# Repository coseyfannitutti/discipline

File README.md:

# DISCIPLINE V2

**65% keyboard assembled with only through hole components, including usb type-c**

**[LICENSE](LICENSE)**

Discipline V2 is licensed under the [Creative Commons Attribution-NonCommercial 4.0 International License](https://creativecommons.org/licenses/by-nc/4.0/). 

This PCB design may be freely reproduced, modified, and manufactured for **PERSONAL USE ONLY** and may not be reproduced in physical form for public sale outside of [CFTKB.com](https://www.cftkb.com). 

If you have built upon this work and have changed the design in a significant way, the non-commercial clause can be waived. If you have developed your own design using files in this repository and would like to sell it, please contact me at bryan@cftkb.com. I fully support those looking to make new things and be creative and will more than likely approve and support your project.

**[BOM, Build Guide, and Flashing Information](./doc)**

**Kits available at [cftkb.com](https://www.cftkb.com)**

**[Optional High Profile Lasercut Acrylic Case](./acrylic-case)**

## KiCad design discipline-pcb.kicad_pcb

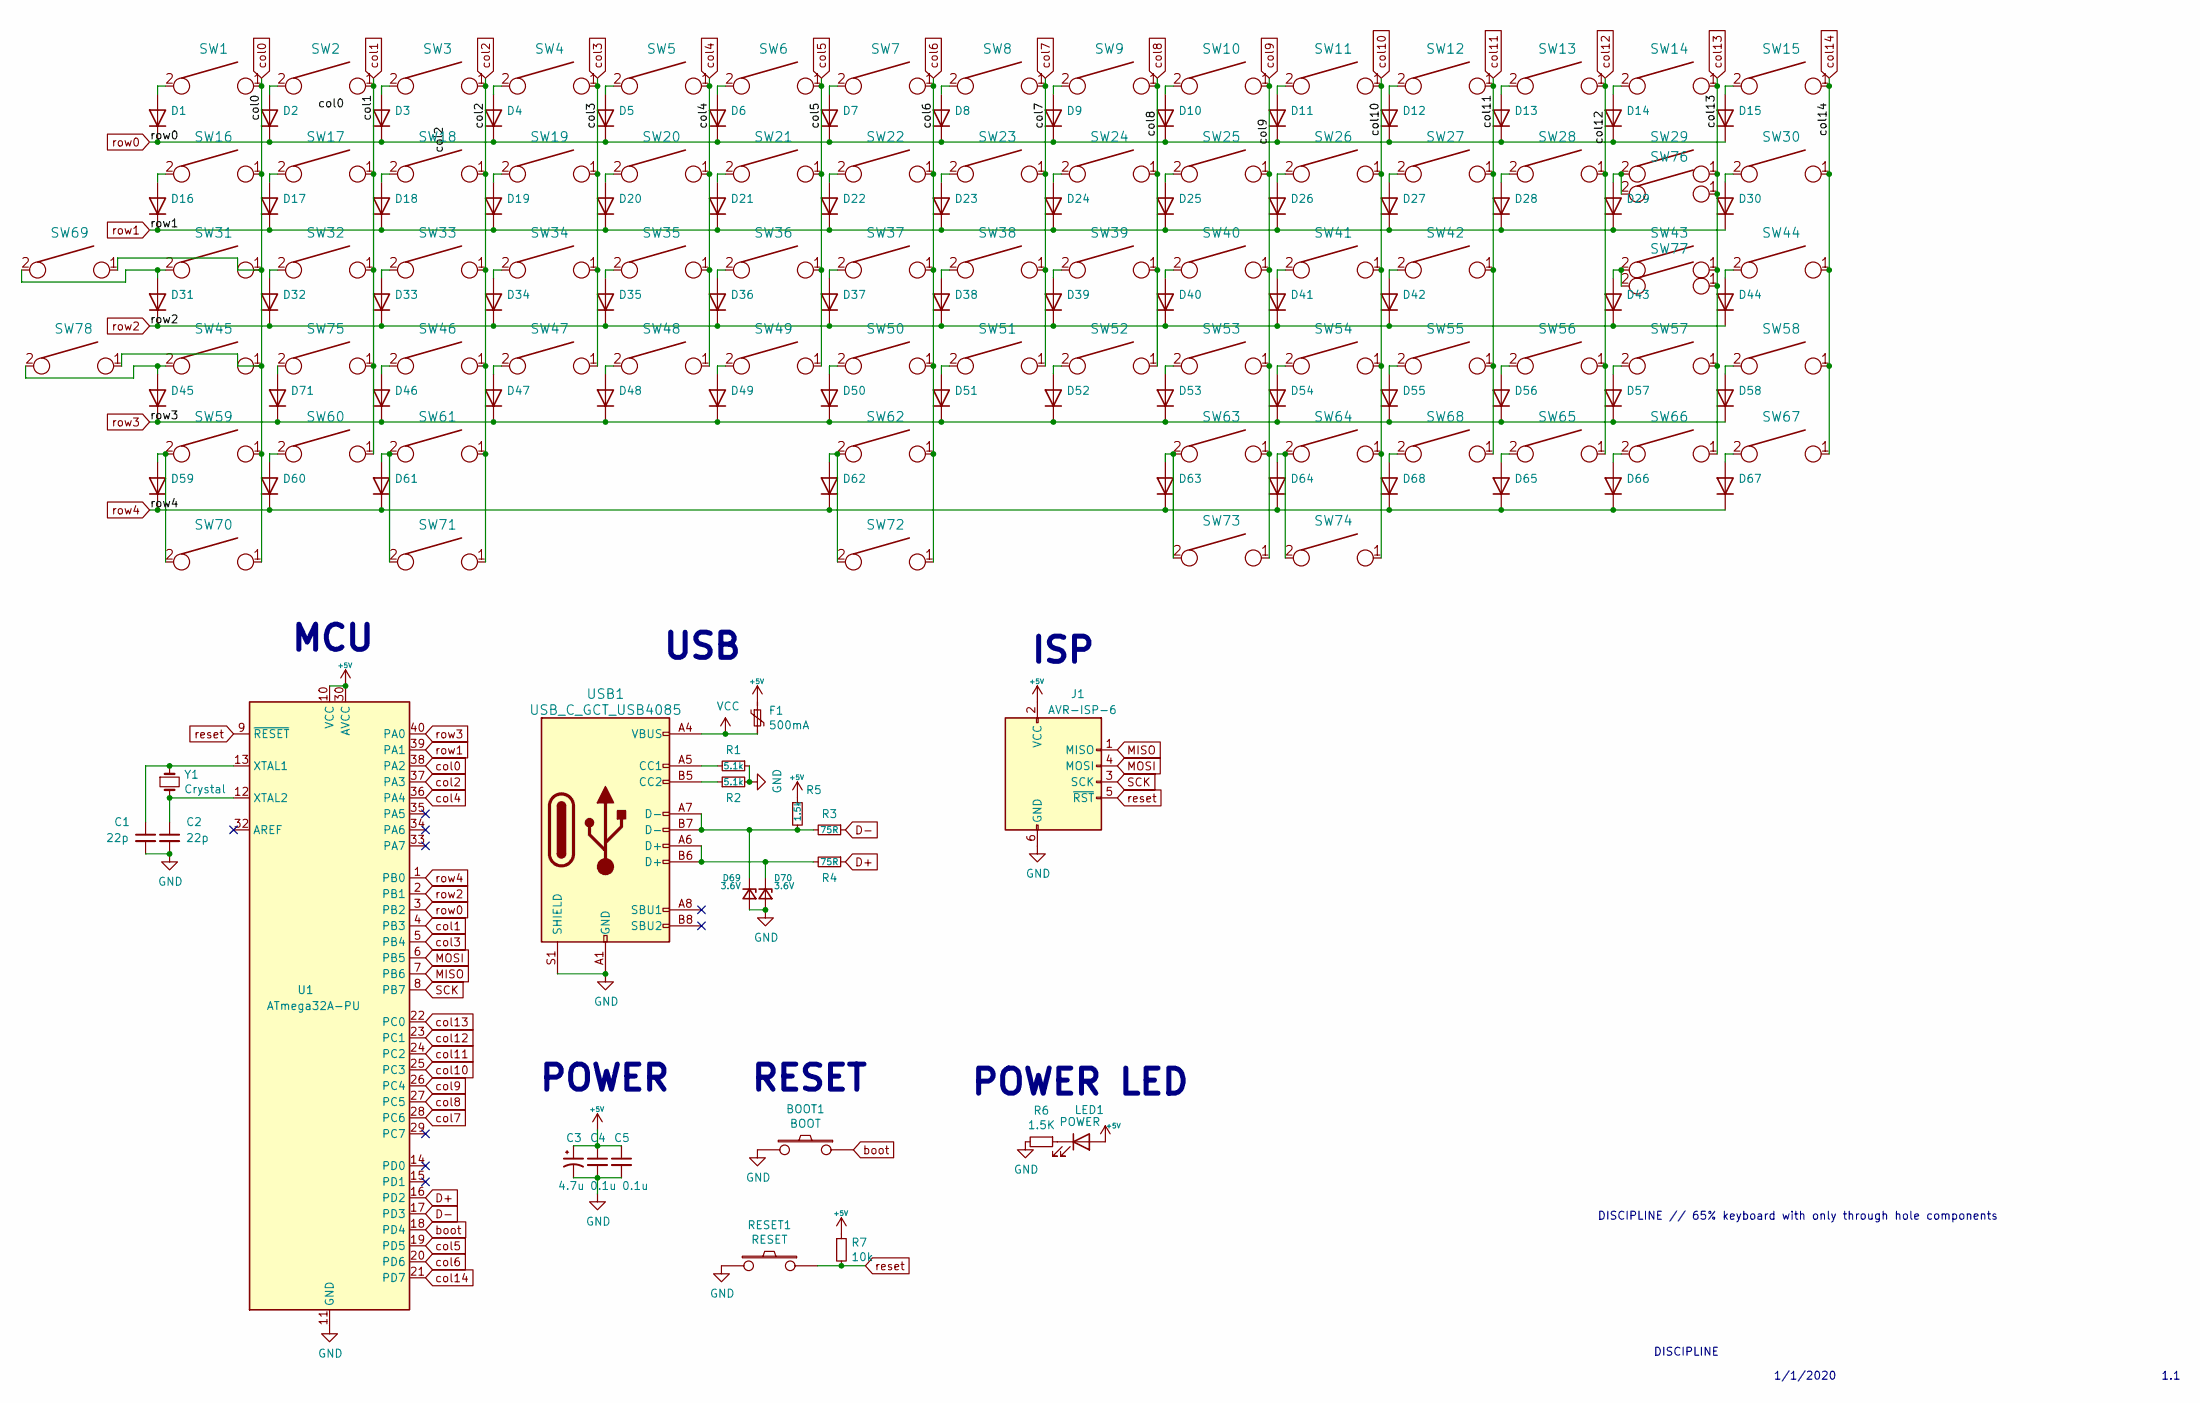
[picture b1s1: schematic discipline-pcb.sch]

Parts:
BOOT1: BOOT; SW_PUSH_6mm
C1, C2: 22p; C_Disc_D3.0mm_W1.6mm_P2.50mm
C3: 4.7u; CP_Radial_D4.0mm_P1.50mm
C4, C5: 0.1u; C_Disc_D4.3mm_W1.9mm_P5.00mm
D1, D2, D3, D4, D5, D6, D7, D8, D9, D10, D11, D12, D13, D14, D15, D16, D17, D18, D19, D20, D21, D22, D23, D24, D25, D26, D27, D28, D29, D30, D31, D32, D33, D34, D35, D36, D37, D38, D39, D40, D41, D42, D43, D44, D45, D46, D47, D48, D49, D50, D51, D52, D53, D54, D55, D56, D57, D58, D59, D60, D61, D62, D63, D64, D65, D66, D67, D68, D71: D_DO-35_SOD27_P5.08mm_Horizontal
D69, D70: 3.6V; D_DO-35_SOD27_P5.08mm_Horizontal
F1: 500mA; polyfuse_5.1mm
J1: AVR-ISP-6; AVR_ICSP_3x2
LED1: POWER; LED_D3.0mm
R1, R2: 5.1k; R_Axial_DIN0204_L3.6mm_D1.6mm_P5.08mm_Horizontal
R3, R4: 75R; R_Axial_DIN0204_L3.6mm_D1.6mm_P5.08mm_Horizontal
R5: 1.5k; R_Axial_DIN0204_L3.6mm_D1.6mm_P5.08mm_Horizontal
R6: 1.5K; R_Axial_DIN0204_L3.6mm_D1.6mm_P5.08mm_Horizontal
R7: 10k; R_Axial_DIN0204_L3.6mm_D1.6mm_P5.08mm_Horizontal
RESET1: RESET; SW_PUSH_6mm
SW1, SW2, SW3, SW4, SW5, SW6, SW7, SW8, SW9, SW10, SW11, SW12, SW13, SW15, SW17, SW18, SW19, SW20, SW21, SW22, SW23, SW24, SW25, SW26, SW27, SW28, SW30, SW32, SW33, SW34, SW35, SW36, SW37, SW38, SW39, SW40, SW41, SW42, SW44, SW46, SW47, SW48, SW49, SW50, SW51, SW52, SW53, SW54, SW55, SW57, SW58, SW62, SW65, SW66, SW67, SW68, SW72, SW75, SW77: KEYSW; SW_Cherry_MX1A_1.00u_PCB-NOSCREEN
SW14: KEYSW; SW_Cherry_MX1A_2.00u_PCBNOSCREEN
SW16, SW29, SW70, SW71, SW73, SW74: KEYSW; SW_Cherry_MX1A_1.50u_PCBNOSCREEN
SW31, SW56: KEYSW; SW_Cherry_MX1A_1.75u_PCBNOSCREEN
SW43, SW45: KEYSW; SW_Cherry_MX1A_2.25u_PCBNOSCREEN
SW59, SW60, SW61, SW63, SW64, SW69, SW78: KEYSW; SW_Cherry_MX1A_1.25u_PCBNOSCREEN
SW76: KEYSW; SW_Cherry_MX1A_ISOEnter_PCB_ReversedStabilizer
U1: ATmega32A-PU; DIP-40_W15.24mm
USB1: USB_C_GCT_USB4085
Y1: Crystal; Crystal_HC49-4H_Vertical

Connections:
+5V: C3.1, C4.1, C5.1, F1.1, J1.2 (VCC), LED1.2 (A), R5.1, R7.1, U1.10 (VCC), U1.30 (AVCC)
D+: R4.1, U1.16 (PD2)
D-: R3.1, U1.17 (PD3)
GND: BOOT1.2, C1.2, C2.2, C3.2, C4.2, C5.2, D69.2 (A), D70.2 (A), J1.6 (GND), R1.1, R2.2, R6.2, RESET1.2, U1.11 (GND), U1.31 (GND), USB1.A1 (GND), USB1.A12 (GND), USB1.B1 (GND), USB1.B12 (GND), USB1.S1 (SHIELD)
MISO: J1.1 (MISO), U1.7 (PB6)
MOSI: J1.4 (MOSI), U1.6 (PB5)
unnamed: C1.1, U1.13 (XTAL1), Y1.1
unnamed: C2.1, U1.12 (XTAL2), Y1.2
unnamed: D1.2 (A), SW1.2
unnamed: D2.2 (A), SW2.2
unnamed: D3.2 (A), SW3.2
unnamed: D4.2 (A), SW4.2
unnamed: D5.2 (A), SW5.2
unnamed: D6.2 (A), SW6.2
unnamed: D7.2 (A), SW7.2
unnamed: D8.2 (A), SW8.2
unnamed: D9.2 (A), SW9.2
unnamed: D10.2 (A), SW10.2
unnamed: D11.2 (A), SW11.2
unnamed: D12.2 (A), SW12.2
unnamed: D13.2 (A), SW13.2
unnamed: D14.2 (A), SW14.2
unnamed: D15.2 (A), SW15.2
unnamed: D16.2 (A), SW16.2
unnamed: D17.2 (A), SW17.2
unnamed: D18.2 (A), SW18.2
unnamed: D19.2 (A), SW19.2
unnamed: D20.2 (A), SW20.2
unnamed: D21.2 (A), SW21.2
unnamed: D22.2 (A), SW22.2
unnamed: D23.2 (A), SW23.2
unnamed: D24.2 (A), SW24.2
unnamed: D25.2 (A), SW25.2
unnamed: D26.2 (A), SW26.2
unnamed: D27.2 (A), SW27.2
unnamed: D28.2 (A), SW28.2
unnamed: D29.2 (A), SW29.2, SW76.2
unnamed: D30.2 (A), SW30.2
unnamed: D31.2 (A), SW31.2, SW69.2
unnamed: D32.2 (A), SW32.2
unnamed: D33.2 (A), SW33.2
unnamed: D34.2 (A), SW34.2
unnamed: D35.2 (A), SW35.2
unnamed: D36.2 (A), SW36.2
unnamed: D37.2 (A), SW37.2
unnamed: D38.2 (A), SW38.2
unnamed: D39.2 (A), SW39.2
unnamed: D40.2 (A), SW40.2
unnamed: D41.2 (A), SW41.2
unnamed: D42.2 (A), SW42.2
unnamed: D43.2 (A), SW43.2, SW77.2
unnamed: D44.2 (A), SW44.2
unnamed: D45.2 (A), SW45.2, SW78.2
unnamed: D46.2 (A), SW46.2
unnamed: D47.2 (A), SW47.2
unnamed: D48.2 (A), SW48.2
unnamed: D49.2 (A), SW49.2
unnamed: D50.2 (A), SW50.2
unnamed: D51.2 (A), SW51.2
unnamed: D52.2 (A), SW52.2
unnamed: D53.2 (A), SW53.2
unnamed: D54.2 (A), SW54.2
unnamed: D55.2 (A), SW55.2
unnamed: D56.2 (A), SW56.2
unnamed: D57.2 (A), SW57.2
unnamed: D58.2 (A), SW58.2
unnamed: D59.2 (A), SW59.2, SW70.2
unnamed: D60.2 (A), SW60.2
unnamed: D61.2 (A), SW61.2, SW71.2
unnamed: D62.2 (A), SW62.2, SW72.2
unnamed: D63.2 (A), SW63.2, SW73.2
unnamed: D64.2 (A), SW64.2, SW74.2
unnamed: D65.2 (A), SW65.2
unnamed: D66.2 (A), SW66.2
unnamed: D67.2 (A), SW67.2
unnamed: D68.2 (A), SW68.2
unnamed: D69.1 (K), R3.2, R5.2, USB1.A7 (D-), USB1.B7 (D-)
unnamed: D70.1 (K), R4.2, USB1.A6 (D+), USB1.B6 (D+)
unnamed: D71.2 (A), SW75.2
unnamed: LED1.1 (K), R6.1
unnamed: R1.2, USB1.A5 (CC1)
unnamed: R2.1, USB1.B5 (CC2)
SCK: J1.3 (SCK), U1.8 (PB7)
VCC: F1.2, USB1.A4 (VBUS), USB1.A9 (VBUS), USB1.B4 (VBUS), USB1.B9 (VBUS)
boot: BOOT1.1, U1.18 (PD4)
col0: SW1.1, SW16.1, SW31.1, SW45.1, SW59.1, SW69.1, SW70.1, SW78.1, U1.38 (PA2)
col1: SW2.1, SW17.1, SW32.1, SW60.1, SW75.1, U1.4 (PB3)
col2: SW3.1, SW18.1, SW33.1, SW46.1, SW61.1, SW71.1, U1.37 (PA3)
col3: SW4.1, SW19.1, SW34.1, SW47.1, U1.5 (PB4)
col4: SW5.1, SW20.1, SW35.1, SW48.1, U1.36 (PA4)
col5: SW6.1, SW21.1, SW36.1, SW49.1, U1.19 (PD5)
col6: SW7.1, SW22.1, SW37.1, SW50.1, SW62.1, SW72.1, U1.20 (PD6)
col7: SW8.1, SW23.1, SW38.1, SW51.1, U1.28 (PC6)
col8: SW9.1, SW24.1, SW39.1, SW52.1, U1.27 (PC5)
col9: SW10.1, SW25.1, SW40.1, SW53.1, SW63.1, SW73.1, U1.26 (PC4)
col10: SW11.1, SW26.1, SW41.1, SW54.1, SW64.1, SW74.1, U1.25 (PC3)
col11: SW12.1, SW27.1, SW42.1, SW55.1, SW68.1, U1.24 (PC2)
col12: SW13.1, SW28.1, SW56.1, SW65.1, U1.23 (PC1)
col13: SW14.1, SW29.1, SW43.1, SW57.1, SW66.1, SW76.1, SW77.1, U1.22 (PC0)
col14: SW15.1, SW30.1, SW44.1, SW58.1, SW67.1, U1.21 (PD7)
reset: J1.5 (~RST), R7.2, RESET1.1, U1.9 (~RESET)
row0: D1.1 (K), D2.1 (K), D3.1 (K), D4.1 (K), D5.1 (K), D6.1 (K), D7.1 (K), D8.1 (K), D9.1 (K), D10.1 (K), D11.1 (K), D12.1 (K), D13.1 (K), D14.1 (K), D15.1 (K), U1.3 (PB2)
row1: D16.1 (K), D17.1 (K), D18.1 (K), D19.1 (K), D20.1 (K), D21.1 (K), D22.1 (K), D23.1 (K), D24.1 (K), D25.1 (K), D26.1 (K), D27.1 (K), D28.1 (K), D29.1 (K), D30.1 (K), U1.39 (PA1)
row2: D31.1 (K), D32.1 (K), D33.1 (K), D34.1 (K), D35.1 (K), D36.1 (K), D37.1 (K), D38.1 (K), D39.1 (K), D40.1 (K), D41.1 (K), D42.1 (K), D43.1 (K), D44.1 (K), U1.2 (PB1)
row3: D45.1 (K), D46.1 (K), D47.1 (K), D48.1 (K), D49.1 (K), D50.1 (K), D51.1 (K), D52.1 (K), D53.1 (K), D54.1 (K), D55.1 (K), D56.1 (K), D57.1 (K), D58.1 (K), D71.1 (K), U1.40 (PA0)
row4: D59.1 (K), D60.1 (K), D61.1 (K), D62.1 (K), D63.1 (K), D64.1 (K), D65.1 (K), D66.1 (K), D67.1 (K), D68.1 (K), U1.1 (PB0)

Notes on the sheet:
DISCIPLINE // 65% keyboard with only through hole components
1/1/2020
DISCIPLINE
1.1
MCU
USB
ISP
POWER
RESET
POWER LED

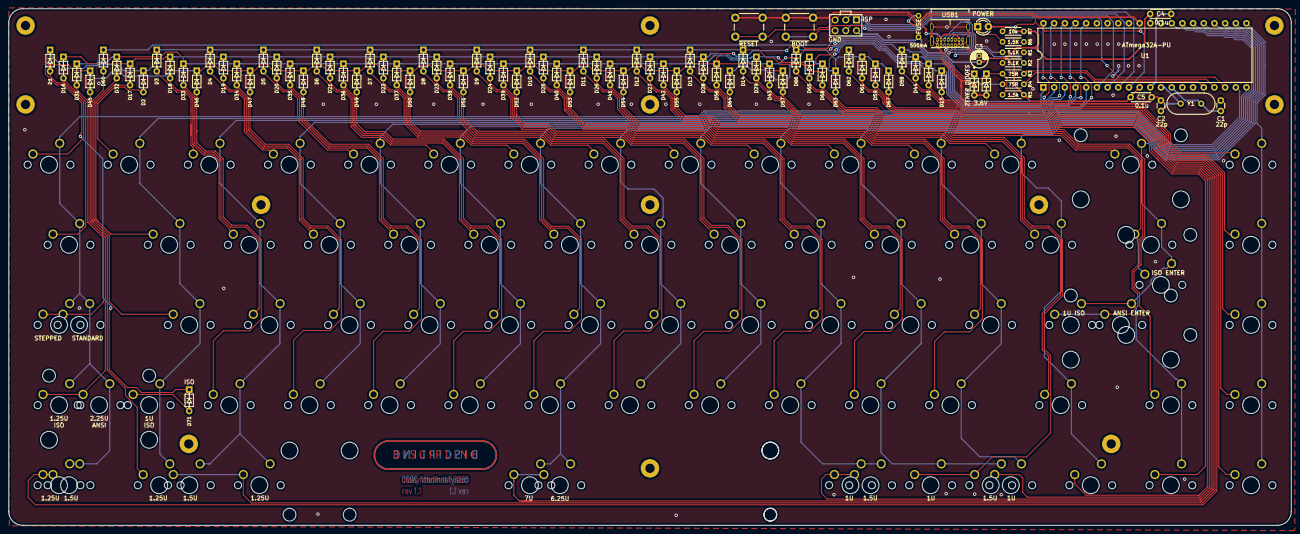
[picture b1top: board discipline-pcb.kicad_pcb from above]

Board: 2 copper layers, 304.9 x 122.8 mm, 170 parts (0 on the bottom side), 106 nets.

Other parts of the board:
ST72: 7U; MX-7U-Stabilizer

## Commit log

2019-07-30 add usbasploader
2019-07-30 move usbasploader to separate repository
2019-07-30 add images
2019-07-30 add build guide and bootloader info
2019-07-31 update screenprint and gerbers
2019-08-01 update images
2019-08-04 clean up symbol labels
2019-08-06 update ic socket 3d model
2019-08-12 fix rctl switch not clipping in
2019-08-12 fix off center screenprint
2019-08-12 update gerbers
2019-08-12 fix off center screenprint and update gerbers
2019-08-15 change fuse value
    change fuse value from 100mA to 500mA. 100mA is fine for this use, but 500mA is USB 2.0 standard
2019-08-17 Update discipline-pcb.kicad_pcb-bak
2019-08-20 edit images
2019-08-22 Update doc
2019-09-16 Update fp-info-cache
2019-09-21 update gerber
2019-10-01 Update sym-lib-table
2019-10-08 Add acrylic plate cutting design
2019-10-08 Support various bottom row sizes
2019-10-08 Union screw hole with stab hole
2019-10-10 add cftkb.pretty
2019-10-10 Create discipline-pcb.sch-bak
2019-10-10 Update discipline-pcb.sch-bak
2019-10-11 Revert "Update discipline-pcb.sch-bak"
    This reverts commit 60fd8acc146e0f24326ca4f8e676ff7e12e92cee.
2019-10-11 Revert "Update discipline-pcb.sch"
    This reverts commit 3febe6e3f5ee2dfceb20178832481c5907b2c946.
2019-10-11 Revert "Update fp-info-cache"
    This reverts commit 3de40be194090145d3c38e5c6a5f46f3c5f6ec4b.
2019-10-11 Revert "Create discipline-pcb.sch-bak"
    This reverts commit 3dc7e60d808c34b2b86821be701f68a6a7846385.
2019-10-11 Revert "Update discipline-pcb.sch"
    This reverts commit a72fcd6089ef7a7854f28251b3b3dd299a3c70af.
2019-10-11 Revert "Update discipline-pcb.pro"
    This reverts commit 51cc2ebde8eba7a8e5a88cedf6e40d973d857545.
2019-10-11 Revert "Update discipline-pcb.kicad_pcb-bak"
    This reverts commit 6f9d74d532aa9e57c588e09e20049bdd6adf1f67.
2019-10-11 Revert "Update discipline-pcb.kicad_pcb"
    This reverts commit 5b5a9406b507a9cf9a6000bfc02bb23341a56901.
2019-10-11 Revert "Update discipline-pcb-cache.lib"
    This reverts commit 5b9b895ae407158b4ad500140b0865a0e21e73d9.
2019-10-12 add schematic symbols for alternate switches so netlist updates properly
2019-10-30 Update link to atmega32a bootloader branch
2019-11-14 Create fp-info-cache
2019-12-15 Update Discipline Plate
2019-12-15 Change to Mini USB port
2019-12-19 mini usb pcb gerbers
2020-02-12 Add case .dxf files
2020-04-20 fix scaling
2020-04-28 add case photo
2020-06-25 Mini USB added
2020-06-26 Update to V2, add ISO support, update license
2020-06-26 update license for rev1.1 (Discipline V2)
2020-06-26 update license for new version (rev1.1/discipline v2)
2020-06-26 update guide links
2020-07-26 Add BOM to the repository
    BOM extracted from octopart page
2020-08-02 Add missing keyboard_parts.lib, fix symbol refs in schematic
2020-08-02 Fix broken ref Y1 on pcb
2021-05-08 Caseless kit Part list
    - Added list of thickness for Acrylic pieces
    - Added Screw list with links (needs proofreading, see comments)
    All information was gathered from closed issues and I felt the need to present it in a simpler way.
    I imitated the style used in the Lasercut Acrylic Case README.
2021-11-06 Proofread the README + Replaced images
2021-11-06 Update README.md
    README paths are case sensitive. Noted.
2024-02-03 added PDFs that were inaccessible due to https://www.cftkb.com expiration
